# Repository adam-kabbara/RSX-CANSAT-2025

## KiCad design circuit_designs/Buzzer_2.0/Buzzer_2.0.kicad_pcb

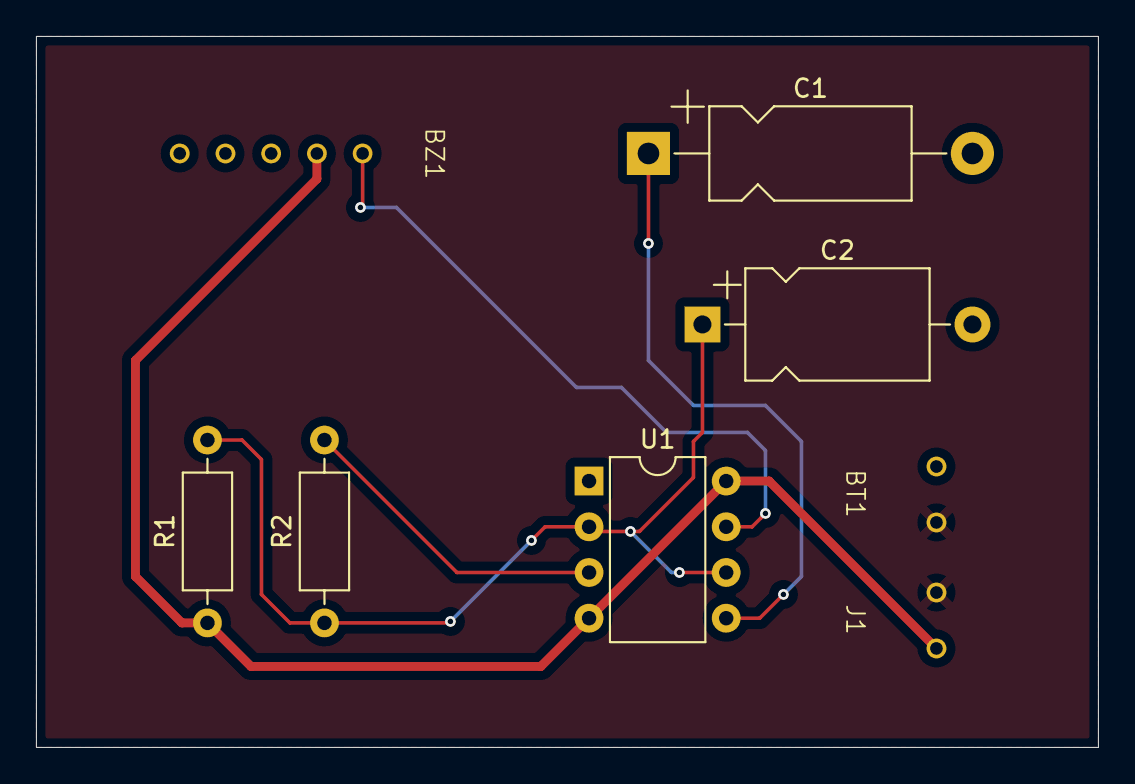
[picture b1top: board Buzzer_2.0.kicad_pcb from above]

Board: 2 copper layers, 59.0 x 39.5 mm, 6 parts (0 on the bottom side), 6 nets.

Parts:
BZ1: Buzzer; Buzzer_Connection
C1: 0.01 μF; CP_Axial_L11.0mm_D5.0mm_P18.00mm_Horizontal
C2: 1 μF; CP_Axial_L10.0mm_D6.0mm_P15.00mm_Horizontal
R1: 100 KΩ; R_Axial_DIN0207_L6.3mm_D2.5mm_P10.16mm_Horizontal
R2: 2.2 KΩ; R_Axial_DIN0207_L6.3mm_D2.5mm_P10.16mm_Horizontal
U1: NE555P; DIP-8_W7.62mm

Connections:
GND: BZ1.3 (G), C1.2, C2.2, U1.1 (GND)
unnamed: BZ1.2 (5V), R1.1, U1.4 (R), U1.8 (VCC)
unnamed: BZ1.1 (Aux), U1.7 (DIS)
unnamed: C1.1, U1.5 (CV)
unnamed: R2.2, U1.3 (Q)
unnamed: C2.1, R1.2, R2.1, U1.2 (TR), U1.6 (THR)
